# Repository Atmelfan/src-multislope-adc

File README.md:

# src-multislope-adc

See [examples](examples).

# Usage
Add the following to your Cargo.toml:
```toml
[dependencies.multislope-adc]
git = "https://github.com/Atmelfan/src-multislope-adc"
tag = v0.1.0
```
If you want to override the default pinout constraints file, add this to your.cargo/config.toml:
```toml
[env]
PCF = { value = "your/pinout.pcf", relative = true }
```

If larger changes are wanted you can try adding the crate as a submodule and add it to your manifest 
using `multislope-adc = { path = "src-multislope-adc", default-features = false }` and build the hdl yourself with a custom top entity.

# Organization
- `rtl` - Hardware design files (gateware)
- `src` - Rust library sources
- `tests` - Rust integration tests

# Tools
1. Yosys with ice40 synthesis, follow [this tutorial](https://projectf.io/posts/building-ice40-fpga-toolchain/).
2. GHDL with synth support, follow [this tutorial](https://ghdl.github.io/ghdl/development/building/index.html)
3. ghdl-yosys-plugin, follow the [README](https://github.com/ghdl/ghdl-yosys-plugin)
4. Cocotb, cocotb-bus, and cocotb-test, follow the [README](https://github.com/cocotb/cocotb) or `pip install -r requirements.txt`

# License
This projects is licensed under CERN Open Hardware Licence Version 2 - Strongly Reciprocal.

See [LICENSE.txt](LICENSE.txt).

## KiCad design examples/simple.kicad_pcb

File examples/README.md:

# multislope-adc examples

# Hardware

# Usage
`cargo run --examples simple -- <args>`

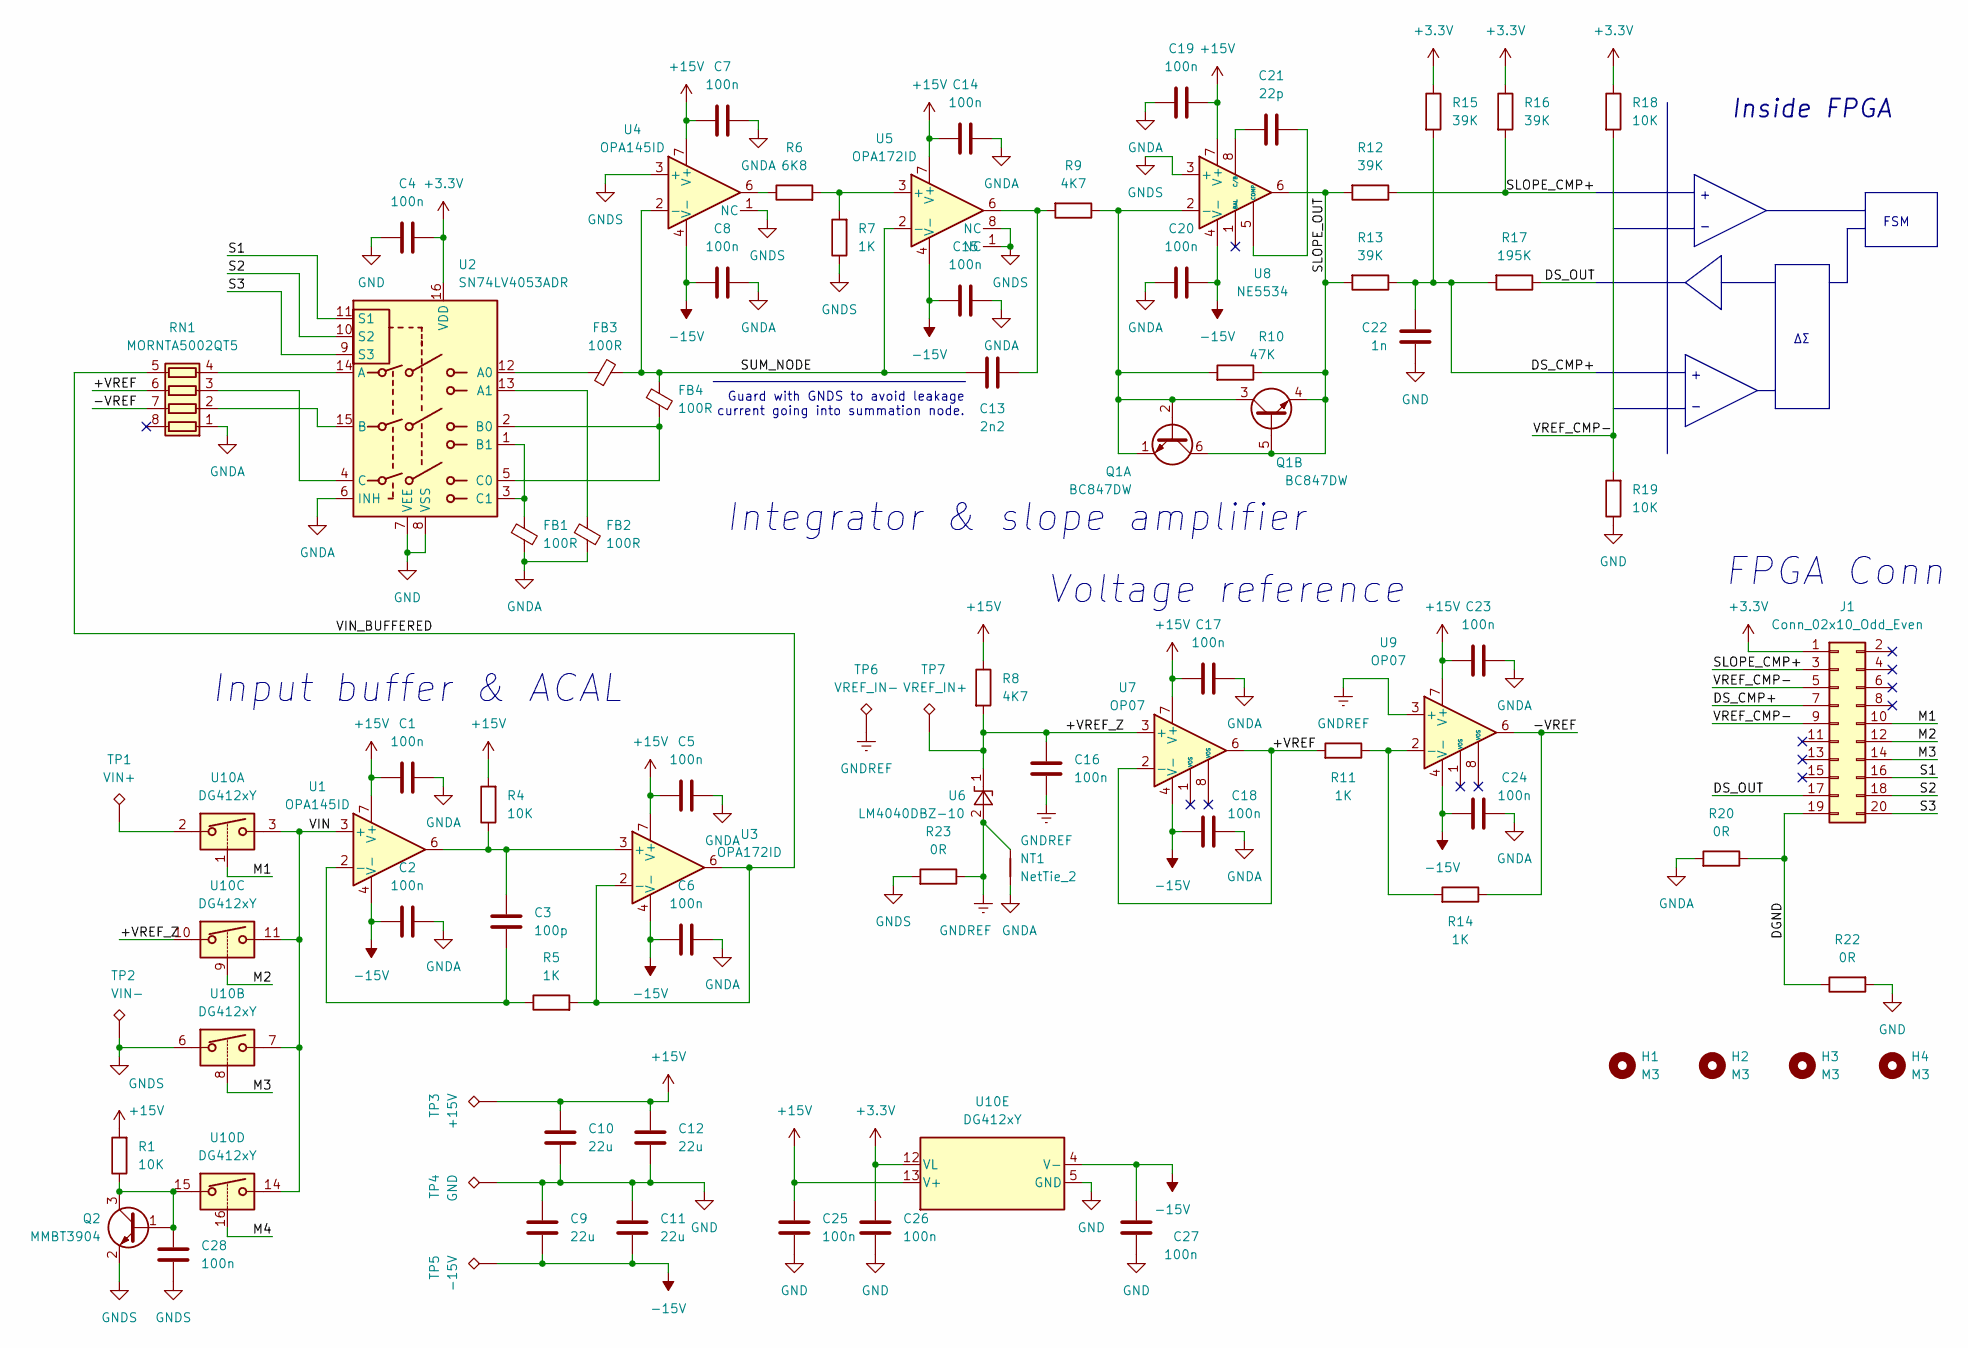
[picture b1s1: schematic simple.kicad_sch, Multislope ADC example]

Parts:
C1, C2, C4, C5, C6, C7, C8, C14, C15, C16, C17, C18, C19, C20, C23, C24, C25, C26, C27, C28: 100n; C_0402_1005Metric_Pad0.74x0.62mm_HandSolder
C3: 100p; C_0603_1608Metric_Pad1.08x0.95mm_HandSolder
C9, C10, C11, C12: 22u; C_1206_3216Metric_Pad1.33x1.80mm_HandSolder
C13: 2n2; C_0805_2012Metric_Pad1.18x1.45mm_HandSolder
C21: 22p; C_0402_1005Metric_Pad0.74x0.62mm_HandSolder
C22: 1n; C_0603_1608Metric_Pad1.08x0.95mm_HandSolder
FB1, FB2, FB3, FB4: 100R; L_0805_2012Metric_Pad1.15x1.40mm_HandSolder
H1, H2, H3, H4: M3; MountingHole_3.2mm_M3
J1: Conn_02x10_Odd_Even; PinSocket_2x10_P2.54mm_Vertical
NT1: NetTie_2; NetTie-2_SMD_Pad0.5mm
Q1: BC847DW; SOT-363_SC-70-6
Q2: MMBT3904; SOT-23
R1, R4, R18, R19: 10K; R_0603_1608Metric_Pad0.98x0.95mm_HandSolder
R5, R7, R11, R14: 1K; R_0603_1608Metric_Pad0.98x0.95mm_HandSolder
R6: 6K8; R_0603_1608Metric_Pad0.98x0.95mm_HandSolder
R8, R9: 4K7; R_0603_1608Metric_Pad0.98x0.95mm_HandSolder
R10: 47K; R_0603_1608Metric_Pad0.98x0.95mm_HandSolder
R12, R13, R15, R16: 39K; R_0603_1608Metric_Pad0.98x0.95mm_HandSolder
R17: 195K; R_0603_1608Metric_Pad0.98x0.95mm_HandSolder
R20, R22, R23: 0R; R_0603_1608Metric_Pad0.98x0.95mm_HandSolder
RN1: MORNTA5002QT5; MSOP-8_3x3mm_P0.65mm
TP1: VIN+; TestPoint_Plated_Hole_D2.0mm
TP2: VIN-; TestPoint_Plated_Hole_D2.0mm
TP3: +15V; TestPoint_Plated_Hole_D2.0mm
TP4: GND; TestPoint_Plated_Hole_D2.0mm
TP5: -15V; TestPoint_Plated_Hole_D2.0mm
TP6: VREF_IN-; TestPoint_Plated_Hole_D2.0mm
TP7: VREF_IN+; TestPoint_Plated_Hole_D2.0mm
U1, U4: OPA145ID; SOIC-8_3.9x4.9mm_P1.27mm
U2: SN74LV4053ADR; SOIC-16_3.9x9.9mm_P1.27mm
U3, U5: OPA172ID; SOIC-8_3.9x4.9mm_P1.27mm
U6: LM4040DBZ-10; SOT-23
U7, U9: OP07; SOIC-8_3.9x4.9mm_P1.27mm
U8: NE5534; SOIC-8_3.9x4.9mm_P1.27mm
U10: DG412xY; SOIC-16_3.9x9.9mm_P1.27mm

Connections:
+3V3: C4.1, C26.1, J1.1, R15.1, R16.1, R18.1, U2.16 (VDD), U10.12 (VL)
+15V: C1.1, C5.1, C7.1, C10.1, C12.1, C14.1, C17.1, C19.1, C23.1, C25.1, R1.2, R4.2, R8.1, TP3.1, U1.7 (V+), U3.7 (V+), U4.7 (V+), U5.7 (V+), U7.7 (V+), U8.7 (V+), U9.7 (V+), U10.13 (V+)
-15V: C2.1, C6.1, C8.1, C9.2, C11.2, C15.1, C18.1, C20.1, C24.1, C27.1, TP5.1, U1.4 (V-), U3.4 (V-), U4.4 (V-), U5.4 (V-), U7.4 (V-), U8.4 (V-), U9.4 (V-), U10.4 (V-)
/+VREF: R11.2, RN1.6 (R3.2), U7.2 (-), U7.6
/+VREF_Z: C16.2, R8.2, TP7.1, U6.1 (K), U7.3 (+), U10.10
/-VREF: R14.1, RN1.7 (R2.2), U9.6
/DGND: J1.19, R20.1, R22.1
/DS_CMP+: C22.2, J1.7, R13.1, R15.2, R17.2
/DS_OUT: J1.17, R17.1
/M1: J1.10, U10.1
/M2: J1.12, U10.9
/M3: J1.14, U10.8
/M4: U10.16
/S1: J1.16, U2.11 (S1)
/S2: J1.18, U2.10 (S2)
/S3: J1.20, U2.9 (S3)
/SLOPE_CMP+: J1.3, R12.1, R16.2
/SLOPE_OUT: Q1.4 (E2), Q1.5 (B2), Q1.6 (C1), R10.1, R12.2, R13.2, U8.6
/SUM_NODE: C13.1, FB3.2, FB4.1, U4.2 (-), U5.2 (-)
/VIN: U1.3 (+), U10.3, U10.7, U10.11, U10.14
/VIN_BUFFERED: R5.2, RN1.5 (R4.2), U3.2 (-), U3.6
/VREF_CMP-: J1.5, J1.9, R18.2, R19.2
GND: C4.2, C9.1, C10.2, C11.1, C12.2, C22.1, C25.2, C26.2, C27.2, R19.1, R22.2, TP4.1, U2.7 (VEE), U2.8 (VSS), U10.5 (GND)
GNDA: C1.2, C2.2, C5.2, C6.2, C7.2, C8.2, C14.2, C15.2, C17.2, C18.2, C19.2, C20.2, C23.2, C24.2, FB1.2, FB2.2, NT1.1, R20.2, RN1.1 (R1.1), U2.6 (INH)
GNDREF: C16.1, NT1.2, R23.1, TP6.1, U6.2 (A), U9.3 (+)
GNDS: C28.1, Q2.2 (E), R7.1, R23.2, TP2.1, U4.1 (NC), U4.3 (+), U5.1 (NC), U5.8 (NC), U8.3 (+), U10.6
unnamed: C3.1, R5.1, U1.2 (-)
unnamed: C3.2, R4.1, U1.6, U3.3 (+)
unnamed: C13.2, R9.2, U5.6
unnamed: C21.1, U8.5 (COMP)
unnamed: C21.2, U8.8 (C/B)
unnamed: C28.2, Q2.1 (B), Q2.3 (C), R1.1, U10.15
unnamed: FB1.1, U2.1 (B1), U2.3 (C1)
unnamed: FB2.1, U2.13 (A1)
unnamed: FB3.1, U2.12 (A0)
unnamed: FB4.2, U2.2 (B0), U2.5 (C0)
unnamed: Q1.1 (E1), Q1.2 (B1), Q1.3 (C2), R9.1, R10.2, U8.2 (-)
unnamed: R6.1, U4.6
unnamed: R6.2, R7.2, U5.3 (+)
unnamed: R11.1, R14.2, U9.2 (-)
unnamed: RN1.2 (R2.1), U2.15 (B)
unnamed: RN1.3 (R3.1), U2.4 (C)
unnamed: RN1.4 (R4.1), U2.14 (A)
unnamed: TP1.1, U10.2

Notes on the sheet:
Integrator & slope amplifier
Guard with GNDS to avoid leakage current going into summation node.
Input buffer & ACAL
Inside FPGA
Voltage reference
FSM
FPGA Conn

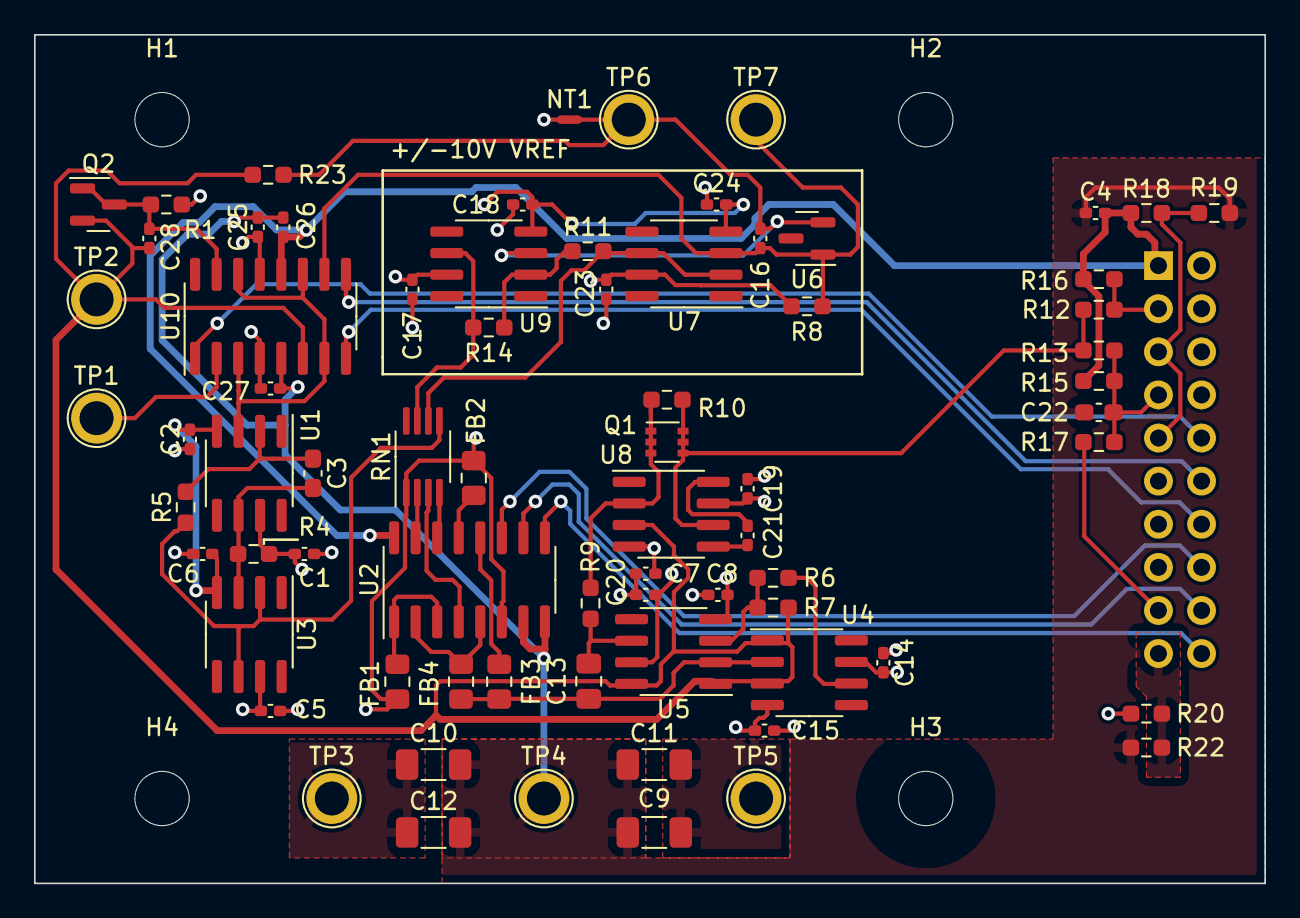
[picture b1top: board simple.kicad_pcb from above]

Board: 4 copper layers, 72.5 x 50.0 mm, 78 parts (1 on the bottom side), 43 nets.

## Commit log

2022-01-10 Idk, a lot.
2022-02-28 I should commit more often
2022-03-01 Started layout
2022-03-01 Changed footprints in schematic
2022-03-02 Layout work
2022-12-22 Finished layout

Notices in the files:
examples/simple.kicad_sch:
SPDX-License-Identifier: CERN-OHL-S-2.0
Copyright (c) 2022
